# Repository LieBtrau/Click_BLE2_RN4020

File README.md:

# RN4020
The RN4020 is a Bluetooth low energy module from Microchip.  The big advantage of this module to most of the other modules on the market which only implement the peripheral role is that the RN4020 also implements the central role.  This opens up a lot of possibilities: You can use the RN4020 in the central role to talk to ble trackers, sensor beacons, ble tags, ...  You could also do RN4020 module to RN4020 module communication, having the advantage that you're using a standard protocol.  This means you can easily add standard bluetooth low energy hardware to your network.  You can use the RN4020 in peripheral role to communicate with your smartphone, tablet, etc. and only using very little power to do that.

For new designs, I would use the RN4870 or RN4871 chipsets.  They contain a reset and some other improvements over the RN4020.

# BLE2 Click
MikroElektronika has made a Click-board for this module.  Unfortunately, their MikroE BLE2-click has some shortcomings.  The BLE2-click board described in this repository has improvements over the original board:
* Connection to reset the board.  The RN4020 doesn't have a reset.  The only way to implement a reset was to do a power toggle.  By sending illegal characters, it's possible to bring the RN4020 in a non-responsive state.  The only way of recovery is a power cycle of the RN4020.
* Connection to the baseboard of the RN4020 activity status.
* WAKE_HW signal connected to the baseboard, so that the RN4020 can be brought back to factory default state.
* CMD/MLDP signal set fix low.  This might hinder full MLDP functionality.  Anyway, if you buy a bluetooth module to do MLDP, you had better spent your money on a NRF24L01+ module.

## Hardware
### BRD161224
* [Schematic](https://github.com/LieBtrau/Click_BLE2_RN4020/raw/master/Hardware/BRD161224/doc/BRD161224_R000x_Schematic.pdf)
* [Assembly Drawing](https://github.com/LieBtrau/Click_BLE2_RN4020/raw/master/Hardware/BRD161224/doc/BRD161224_R00_AssemblyDrawing_top.pdf)
* [Drill Plan](https://github.com/LieBtrau/Click_BLE2_RN4020/raw/master/Hardware/BRD161224/doc/BRD161224_R00_DrillPlan.pdf)
* [Film top](https://github.com/LieBtrau/Click_BLE2_RN4020/raw/master/Hardware/BRD161224/doc/BRD161224_R00_Film_top.pdf)
* [Film bottom](https://github.com/LieBtrau/Click_BLE2_RN4020/raw/master/Hardware/BRD161224/doc/BRD161224_R00_Film_bot.pdf)

---

## Software

* Central & peripheral functionality implemented (and tested on Nucleo STM32F103).
* Use of private characteristics

This library is based on the MikroE library which is far from complete or usable.  It only holds functions to send data to the RN4020.  There's no functionality to parse the response from the RN4020.

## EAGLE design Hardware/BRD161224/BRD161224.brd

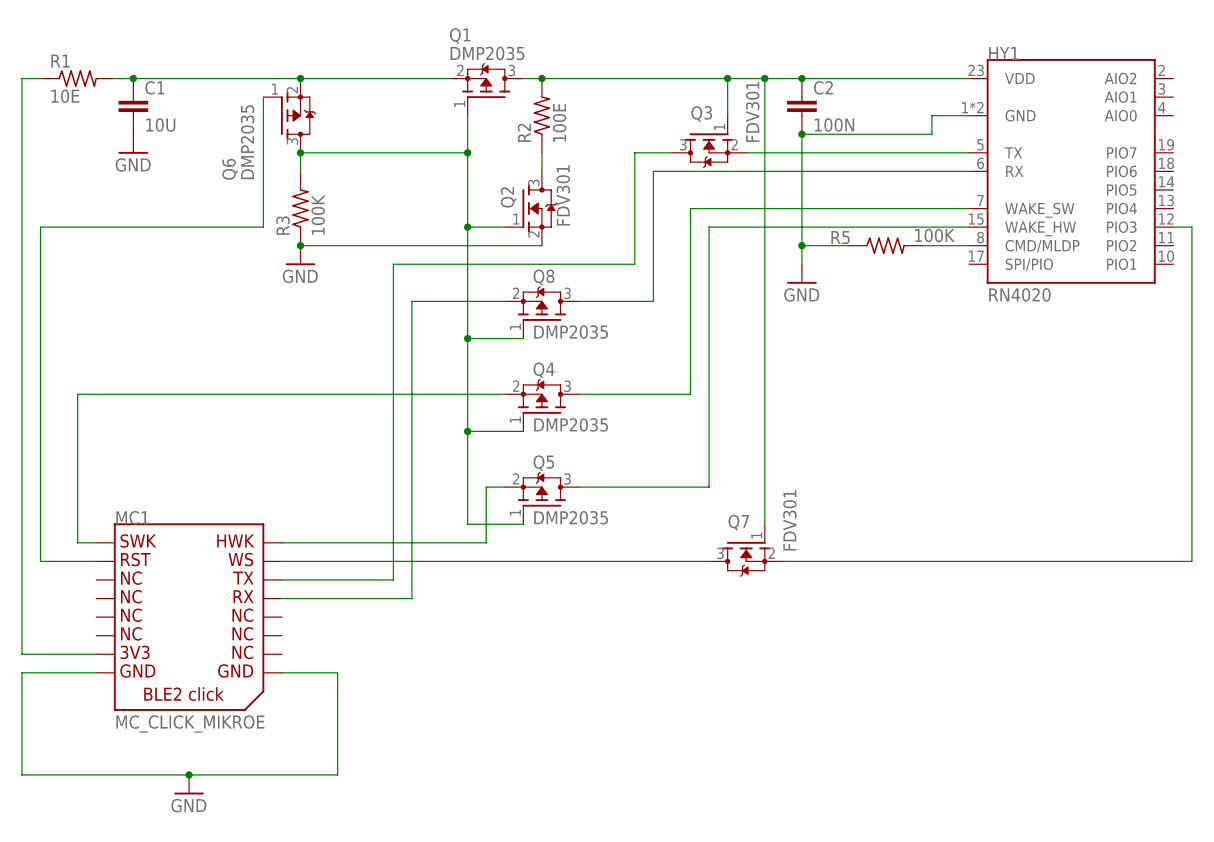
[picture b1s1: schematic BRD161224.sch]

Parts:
C1: 10U; CA_1206
C2: 100N; CA_1206
HY1: RN4020; HY_BLE_RN4020
MC1: MC_CLICK_MIKROE
Q1, Q4, Q5, Q6, Q8: DMP2035; SC_SOT23
Q2, Q3, Q7: FDV301; SC_SOT23
R1: 10E; RE_1206
R2: 100E; RE_1206
R3, R5: 100K; RE_1206

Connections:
GND: C1.2, C2.2, HY1.1 (GND), HY1.24 (GND), MC1.P$8 (8), MC1.P$9, Q2.2 (S), R3.1, R5.1
unnamed: C1.1, Q1.2 (S), Q6.2 (S), R1.2
unnamed: C2.1, HY1.23 (VDD), Q1.3 (D), Q3.1 (G), Q7.1 (G), R2.2
unnamed: Q2.3 (D), R2.1
unnamed: Q1.1 (G), Q2.1 (G), Q4.1 (G), Q5.1 (G), Q6.3 (D), Q8.1 (G), R3.2
unnamed: MC1.P$7, R1.1
unnamed: MC1.P$2, Q6.1 (G)
unnamed: HY1.5 (TX), Q3.2 (S)
unnamed: MC1.P$13, Q8.2 (S)
unnamed: MC1.P$14, Q3.3 (D)
unnamed: HY1.12 (PIO3), Q7.2 (S)
unnamed: HY1.8 (CMD/MLDP), R5.2
unnamed: HY1.7 (WAKE_SW), Q4.3 (D)
unnamed: HY1.15 (WAKE_HW), Q5.3 (D)
unnamed: MC1.P$1, Q4.2 (S)
unnamed: HY1.6 (RX), Q8.3 (D)
unnamed: MC1.P$16, Q5.2 (S)
unnamed: MC1.P$15, Q7.3 (D)

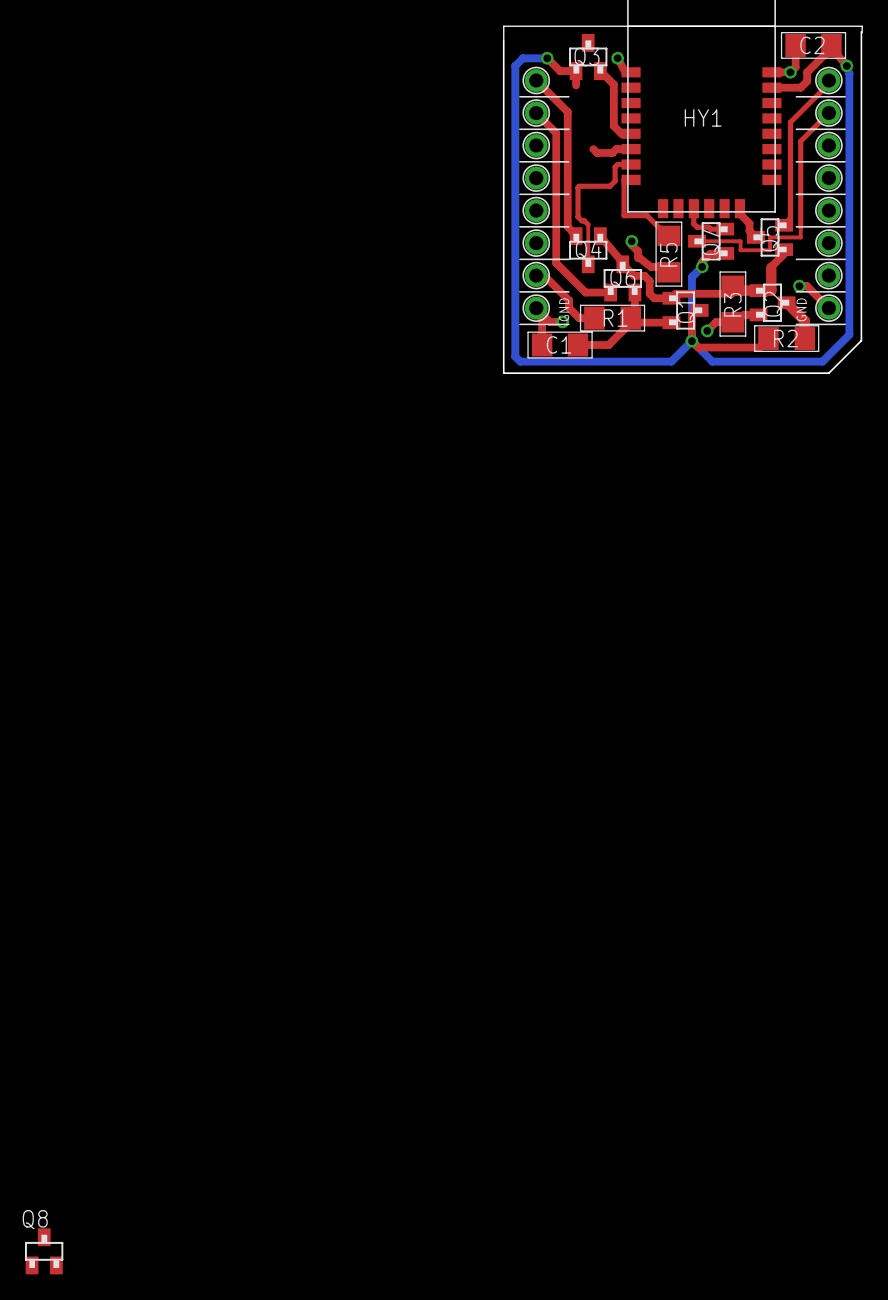
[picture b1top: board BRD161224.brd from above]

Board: 2 copper layers, 28.0 x 27.1 mm, 18 parts (0 on the bottom side), 18 nets.

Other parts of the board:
DRILEGEND: DRILEGEND
U$2: MC_FRAME_A5

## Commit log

2016-05-13 Added readme
2016-07-10 UART communication working HW-reset implemented
2016-07-19 Preliminary version that sets up communication parameters. Works at 2400baud. Signed-off-by: Christoph Tack <prog.send@gmail.com>
2016-07-24 library works more reliably with HardwareSerial than with SoftwareSerial
2016-07-25 Working version that can restore the module from unknown or locked state.
2016-07-27 Waiting for reply from module can now read multiple lines.
2016-07-29 removing CTS-functionality adding status updates adding getting handle of UUID service+characteristic
2016-07-30 general set function replaced by specific set functions. These hide the internals of the RN4020 module.
2016-07-30 adding operating mode switch
2016-07-31 Connection event implemented
2016-08-02 Adding bluetooth characteristic objects with callback
2016-08-02 Adding private characteristic
2016-08-04 Adding private characteristics works
2016-08-07 -bug fix in HAL-layer -Making code compatible with Nucleo-STM32F1 platform
2016-08-11 Updating handles of characteristics works
2016-08-13 Remote updating of characteristics works fine
2016-08-23 Adding getter for MAC-address of the RN4020
2016-08-25 Adding setting of Bluetooth device name
2016-09-04 Finding devices works
2016-09-05 Parsing advertisements works
2016-09-11 getting bonding parameters works
2016-09-13 bonding and rebonding works
2016-12-25 Schematic look ready
2016-12-27 ble2_click R00 finished
2016-12-27 Replacing the original RN4020 description
    MikroE description is not applicable to this repository. Replacing it by updated info from this repository.
2016-12-27 Removing old MikroE examples
2016-12-28 Compiling example works
2016-12-29 Closing and reopening serial port fixed without losing characters (by adding a fix timeout)
2016-12-31 Improvements for reliability of connection setup and bonding
2017-01-03 Client writing characteristic of a remote server.
2017-01-03 Central reads characteristic from peripheral
2017-01-04 Removing some magical numbers
2017-01-04 cleaning up
2017-01-04 Fix for peripherals with low advertisement rate
2017-01-05 ongoing work
2017-01-07 When starting up when all characteristics and services have already been created, there is no list of services and characteristics in MCU memory.
2017-01-07 Fixed the event triggering when a characteristic has been written by a remote client
2017-01-10 Fixing bug: advertising was not restarted after a closed connection that followed upon a failed bonding action.
2017-01-10 Making use of characteristics ready for more general applications.
2017-01-11 fixing bug in gotLine (when reading multiple lines)
2017-01-12 Implementing read of local characteristic
2017-01-12 implemented writing local characteristics
2017-01-13 Fixing functionality of central: listing advertisements + waiting for connection
2017-01-14 implementing: get bonded status
2017-01-14 removing unused event
2017-01-14 update after finish development on library
2017-01-15 Fix for peripheral mode
2017-01-15 Fix for factory default Fix for parsing passcode
2017-05-03 Updating to Eagle 8.1.1 Adding two drill holes for easier mounting of pin headers Adding output files
2017-05-03 Update & clarifying
2017-07-14 Schematic: replacing D1, R7 and R4 by Q8.
2017-07-15 * Code compiles & runs on Blue Pill * Debugging works as well * Functionality not ok.
2017-07-19 Inverting power on for Click BLE2 to fix application
2017-07-26 Reorganizing library and example
2017-07-28 Moving file, adding an example
2017-07-28 fixing sketch (function restored)
2017-07-31 removing debug source
2017-08-15 -MAC-address stored as 6 bytes, not string. -resetting buffers was not done everywhere.
2017-08-16 Fixes for bonding the modules
2017-08-20 improvements for bonding
2017-08-20 writing multiple bytes to characteristic
2017-09-19 Enabling other baudrates for UART
2017-09-24 Further speeding up BLE startup cleaning up some code
2017-09-28 fix bug in connection state
2017-10-13 Adding GPIO to verify connectivity
2017-10-13 -GPIO can be used to verify connection -adding a quick way to read MAC-address
2017-10-21 - fixing wrong baudrates at startup - making proper disconnections
2017-10-29 Cleaning up advertizing code Adding data validity check on reading local characteristics.
